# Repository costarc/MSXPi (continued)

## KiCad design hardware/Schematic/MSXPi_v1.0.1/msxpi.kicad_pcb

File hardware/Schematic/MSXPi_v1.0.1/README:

1.0.3 - Shifted PCB holes to better fit in Patola (Brazilian) case & added 3rd mounting hole
1.0.2 - Changed footprint to smaller size to help reducing manufacturing costs
1.0.1 - Changed ROM from 27C256 to AT28C256 with hability to be programmed from MSX-DOs
1.0 - PCB Changes from Rev.7

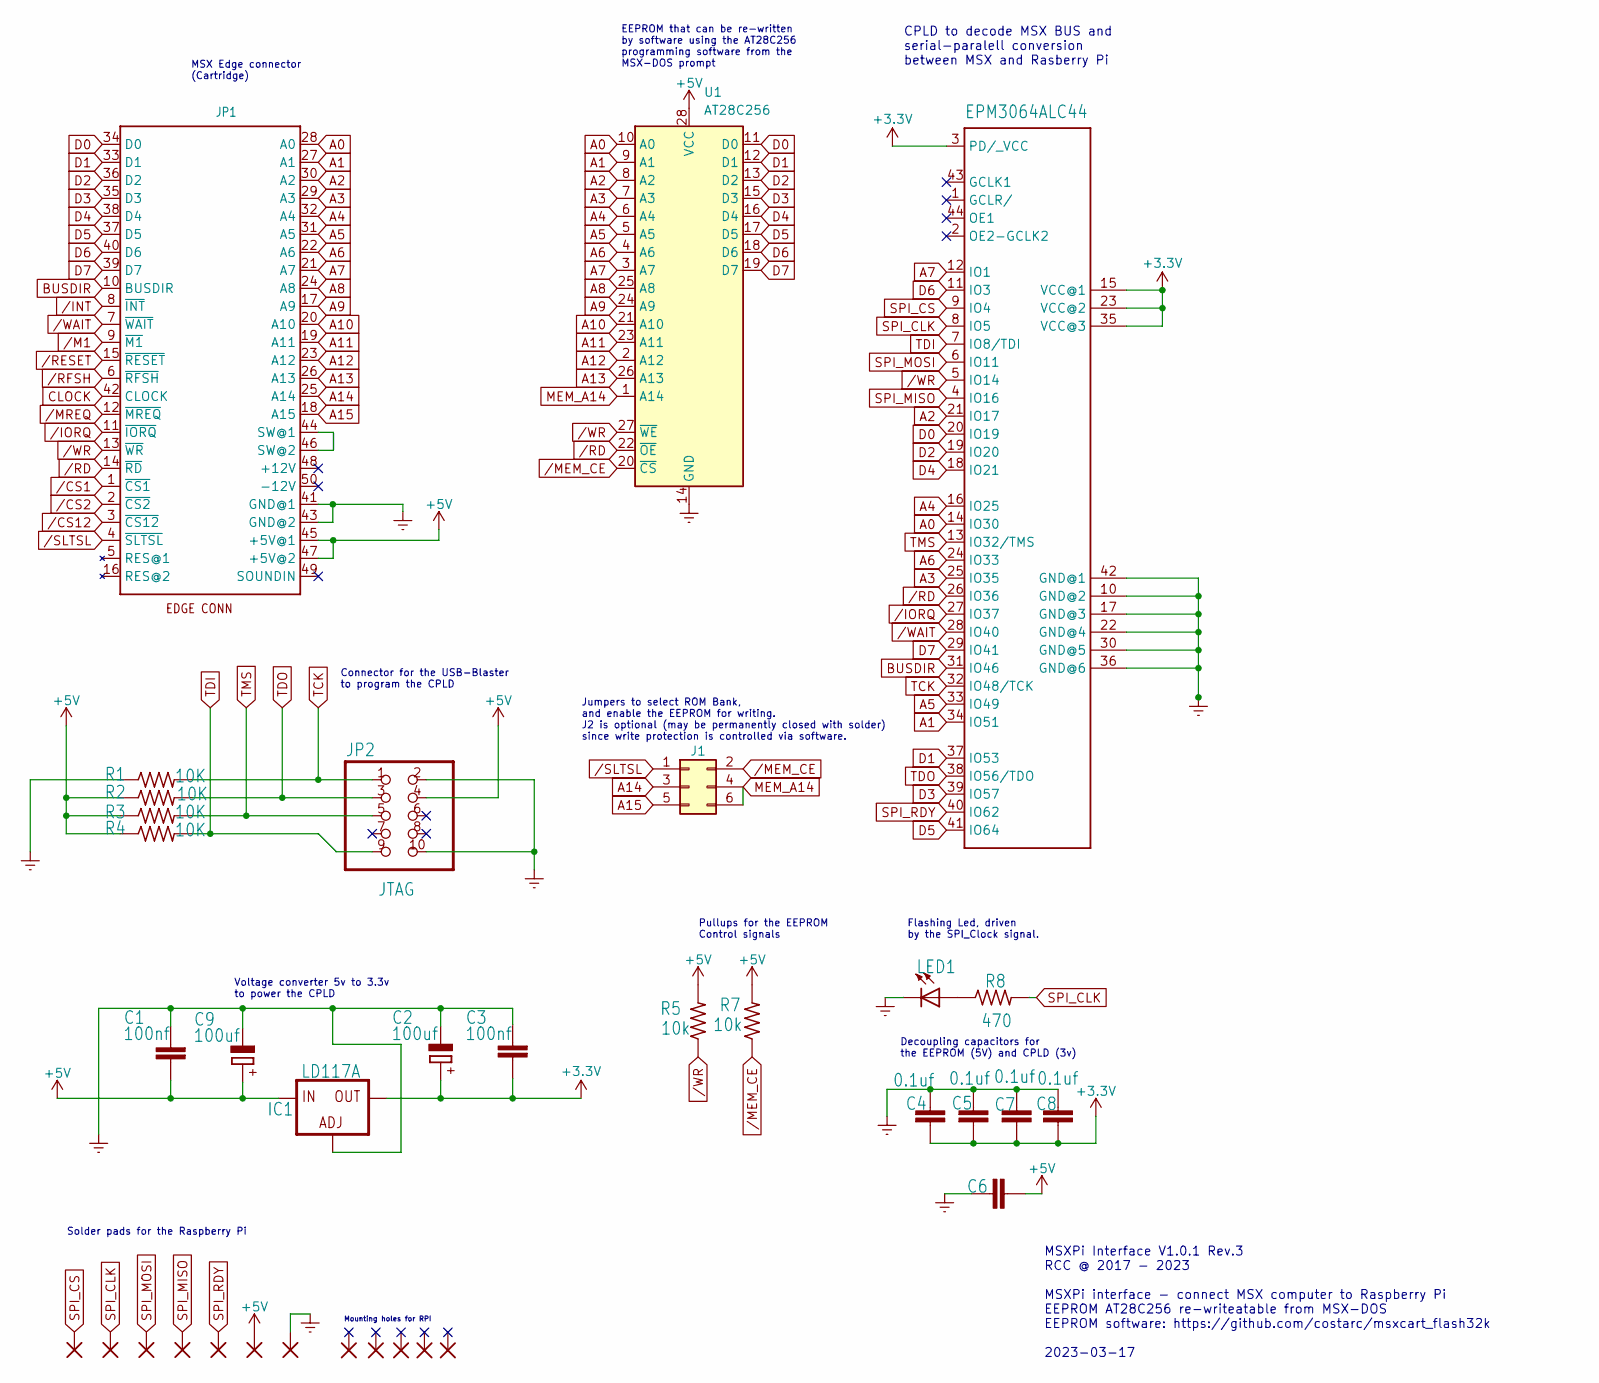
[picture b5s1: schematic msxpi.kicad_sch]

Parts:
+5V1: 2,15/1,0; 2,15_1,0
C1, C3: 100nf; C2.5-3
C2, C9: 100uf; E2,5-5
C4, C5, C6, C7, C8: 0.1uf; C2.5-3
EPM3064ALC44: EPM3064ALC44; PLCC-S44
GND5: 2,15/1,0; 2,15_1,0
IC1: LD117A; SOT-223-3_TabPin2
J1: ROM_SWITCH; PinHeader_2x03_P2.54mm_Vertical
JP1: MSXCART1; MSX_CART_SW_Official_3Holes
JP2: JTAG; IDC-Header_2x05_P2.54mm_Horizontal
LED1: LED3MM
MOUNTHOLE1, MOUNTHOLE2, MOUNTHOLE3, MOUNTHOLE4, MOUNTHOLE5: 2,15/1,0; 2,15_1,0
R1, R2, R3, R4: 10K; 0207_7
R5, R7: 10k; 0207_7
R8: 470; 0207_7
SPI_CLK_PI_GPIO1: SPI_CLK; 2,15_1,0
SPI_CS_PI_GPIO1: SPI_CS; 2,15_1,0
SPI_MISO_PI_GPIO1: SPI_MISO; 2,15_1,0
SPI_MOSI_PI_GPIO1: SPI_MOSI; 2,15_1,0
SPI_RDY_PI_GPIO1: SPI_RDY; 2,15_1,0
U1: AT28C256; DIP-28_W15.24mm

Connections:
+3.3V: C2.+, C3.1, C4.2, C5.2, C7.2, C8.2, EPM3064ALC44.3 (PD/_VCC), EPM3064ALC44.15 (VCC@1), EPM3064ALC44.23 (VCC@2), EPM3064ALC44.35 (VCC@3), IC1.2 (OUT)
+5V: +5V1.1, C1.1, C6.1, C9.+, IC1.3 (IN), JP1.45 (+5V@1), JP1.47 (+5V@2), JP2.4, R2.1, R3.1, R4.1, R5.2, R7.2, U1.28 (VCC)
A0: EPM3064ALC44.14 (IO30), JP1.28 (A0), U1.10 (A0)
A1: EPM3064ALC44.34 (IO51), JP1.27 (A1), U1.9 (A1)
A2: EPM3064ALC44.21 (IO17), JP1.30 (A2), U1.8 (A2)
A3: EPM3064ALC44.25 (IO35), JP1.29 (A3), U1.7 (A3)
A4: EPM3064ALC44.16 (IO25), JP1.32 (A4), U1.6 (A4)
A5: EPM3064ALC44.33 (IO49), JP1.31 (A5), U1.5 (A5)
A6: EPM3064ALC44.24 (IO33), JP1.22 (A6), U1.4 (A6)
A7: EPM3064ALC44.12 (IO1), JP1.21 (A7), U1.3 (A7)
A8: JP1.24 (A8), U1.25 (A8)
A9: JP1.17 (A9), U1.24 (A9)
A10: JP1.20 (A10), U1.21 (A10)
A11: JP1.19 (A11), U1.23 (A11)
A12: JP1.23 (A12), U1.2 (A12)
A13: JP1.26 (A13), U1.26 (A13)
A14: J1.3, JP1.25 (A14)
A15: J1.5, JP1.18 (A15)
BUSDIR: EPM3064ALC44.31 (IO46), JP1.10 (BUSDIR)
CLOCK: JP1.42 (CLOCK)
D0: EPM3064ALC44.20 (IO19), JP1.34 (D0), U1.11 (D0)
D1: EPM3064ALC44.37 (IO53), JP1.33 (D1), U1.12 (D1)
D2: EPM3064ALC44.19 (IO20), JP1.36 (D2), U1.13 (D2)
D3: EPM3064ALC44.39 (IO57), JP1.35 (D3), U1.15 (D3)
D4: EPM3064ALC44.18 (IO21), JP1.38 (D4), U1.16 (D4)
D5: EPM3064ALC44.41 (IO64), JP1.37 (D5), U1.17 (D5)
D6: EPM3064ALC44.11 (IO3), JP1.40 (D6), U1.18 (D6)
D7: EPM3064ALC44.29 (IO41), JP1.39 (D7), U1.19 (D7)
GNDREF: C1.2, C2.-, C3.2, C4.1, C5.1, C6.2, C7.1, C8.1, C9.-, EPM3064ALC44.10 (GND@2), EPM3064ALC44.17 (GND@3), EPM3064ALC44.22 (GND@4), EPM3064ALC44.30 (GND@5), EPM3064ALC44.36 (GND@6), EPM3064ALC44.42 (GND@1), GND5.1, IC1.1 (ADJ), JP1.41 (GND@1), JP1.43 (GND@2), JP2.2, JP2.10, LED1.K (C), R1.1, U1.14 (GND)
MEM_A14: J1.4, J1.6, U1.1 (A14)
unnamed: JP1.44 (SW@1), JP1.46 (SW@2)
unnamed: LED1.A, R8.1
SPI_CLK: EPM3064ALC44.8 (IO5), R8.2, SPI_CLK_PI_GPIO1.1
SPI_CS: EPM3064ALC44.9 (IO4), SPI_CS_PI_GPIO1.1
SPI_MISO: EPM3064ALC44.4 (IO16), SPI_MISO_PI_GPIO1.1
SPI_MOSI: EPM3064ALC44.6 (IO11), SPI_MOSI_PI_GPIO1.1
SPI_RDY: EPM3064ALC44.40 (IO62), SPI_RDY_PI_GPIO1.1
TCK: EPM3064ALC44.32 (IO48/TCK), JP2.1, R1.2
TDI: EPM3064ALC44.7 (IO8/TDI), JP2.9, R4.2
TDO: EPM3064ALC44.38 (IO56/TDO), JP2.3, R2.2
TMS: EPM3064ALC44.13 (IO32/TMS), JP2.5, R3.2
/CS1: JP1.1 (~CS1)
/CS2: JP1.2 (~CS2)
/CS12: JP1.3 (~CS12)
/INT: JP1.8 (~INT)
/IORQ: EPM3064ALC44.27 (IO37), JP1.11 (~IORQ)
/M1: JP1.9 (~M1)
/MEM_CE: J1.2, R7.1, U1.20 (~CS)
/MREQ: JP1.12 (~MREQ)
/RD: EPM3064ALC44.26 (IO36), JP1.14 (~RD), U1.22 (~OE)
/RESET: JP1.15 (~RESET)
/RFSH: JP1.6 (~RFSH)
/SLTSL: J1.1, JP1.4 (~SLTSL)
/WAIT: EPM3064ALC44.28 (IO40), JP1.7 (~WAIT)
/WR: EPM3064ALC44.5 (IO14), JP1.13 (~WR), R5.1, U1.27 (~WE)

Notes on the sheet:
Decoupling capacitors for the EEPROM (5V) and CPLD (3v)
Flashing Led, driven by the SPI_Clock signal.
Jumpers to select ROM Bank, and enable the EEPROM for writing. J2 is optional (may be permanently closed with solder) since write protection is controlled via software.
EEPROM that can be re-written by software using the AT28C256 programming software from the MSX-DOS prompt
Pullups for the EEPROM Control signals
Solder pads for the Raspberry Pi
MSXPi Interface V1.0.1 Rev.3 RCC @ 2017 - 2023 MSXPi interface - connect MSX computer to Raspberry Pi EEPROM AT28C256 re-writeatable from MSX-DOS EEPROM software: https://github.com/costarc/msxcart_flash32k 2023-03-17
MSX Edge connector (Cartridge)
Connector for the USB-Blaster to program the CPLD
Voltage converter 5v to 3.3v to power the CPLD
Mounting holes for RPI
CPLD to decode MSX BUS and serial-paralell conversion between MSX and Rasberry Pi

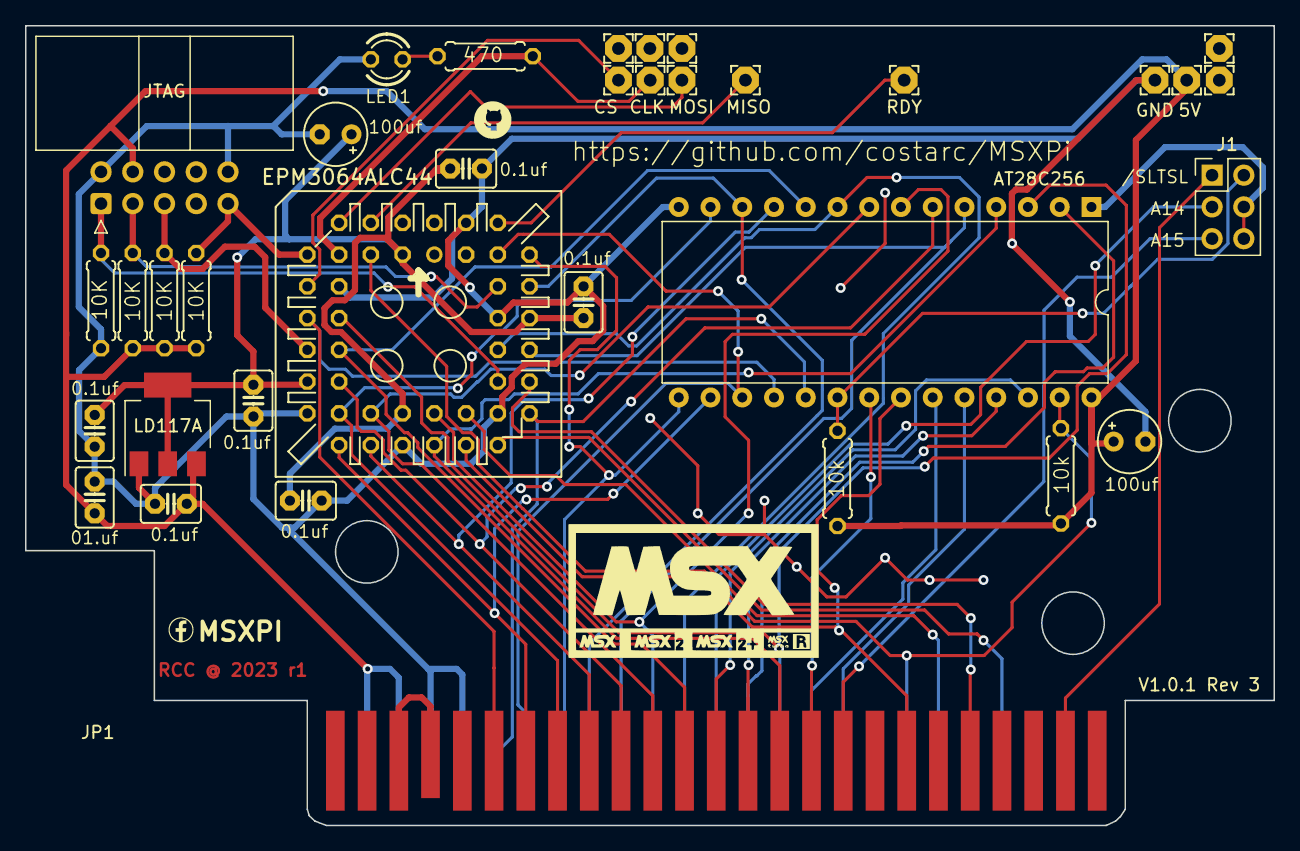
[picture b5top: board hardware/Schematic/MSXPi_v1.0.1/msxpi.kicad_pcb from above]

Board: 2 copper layers, 99.9 x 64.0 mm, 35 parts (0 on the bottom side), 46 nets.

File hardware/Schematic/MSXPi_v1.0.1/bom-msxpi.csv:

"Source:","C:\Users\alpha\Documents\Dev\MSXPi\hardware\Schematic\MSXPi_v0.7.0_Rev_7b\msxpi.kicad_sch"
"Date:","17/11/2022 13:43:14"
"Tool:","Eeschema (6.0.7)"
"Generator:","C:\KiCad\6.0\bin\scripting\plugins/bom_csv_grouped_by_value_with_fp.py"
"Component Count:","36"
"Ref","Qnty","Value","Cmp name","Footprint","Description","Vendor"
"+5V1, ","1","2,15/1,0","2,15{slash}1,0","msxpi:2,15_1,0","",""
"C1, C3, ","2","100nf","C2,5-3","msxpi:C2.5-3","",""
"C2, C9, ","2","100uf","CPOL-EUE2.5-5","msxpi:E2,5-5","",""
"C4, C5, C6, C7, C8, ","5","0.1uf","C2,5-3","msxpi:C2.5-3","",""
"EPM3064ALC44, ","1","EPM3064ALC44","EPM3064S44","msxpi:PLCC-S44","",""
"GND5, ","1","2,15/1,0","2,15{slash}1,0","msxpi:2,15_1,0","",""
"IC1, ","1","LD117A","LD117A?V","Package_TO_SOT_SMD:SOT-223-3_TabPin2","",""
"J1, ","1","ROM_SWITCH","Conn_02x07_Odd_Even","Connector_PinHeader_2.54mm:PinHeader_2x07_P2.54mm_Vertical","Generic connector, double row, 02x07, odd/even pin numbering scheme (row 1 odd numbers, row 2 even numbers), script generated (kicad-library-utils/schlib/autogen/connector/)",""
"JP1, ","1","MSXCART1","MSXCART1","Roni Footprints:MSX_CART","",""
"JP2, ","1","JTAG","PINHD-2X5{slash}90","Connector_IDC:IDC-Header_2x05_P2.54mm_Horizontal","",""
"LED1, ","1","LED3MM","LED3MM","msxpi:LED3MM","",""
"MOUNTHOLE1, MOUNTHOLE2, MOUNTHOLE3, MOUNTHOLE4, MOUNTHOLE5, ","5","2,15/1,0","2,15{slash}1,0","msxpi:2,15_1,0","",""
"R1, R2, R3, R4, ","4","10K","R-US_0207{slash}7","msxpi:0207_7","",""
"R5, R6, R7, ","3","10k","R-US_0207{slash}7","msxpi:0207_7","",""
"R8, ","1","470","R-US_0207{slash}7","msxpi:0207_7","",""
"SPI_CLK_PI_GPIO1, ","1","SPI_CLK","2,15{slash}1,0","msxpi:2,15_1,0","",""
"SPI_CS_PI_GPIO1, ","1","SPI_CS","2,15{slash}1,0","msxpi:2,15_1,0","",""
"SPI_MISO_PI_GPIO1, ","1","SPI_MISO","2,15{slash}1,0","msxpi:2,15_1,0","",""
"SPI_MOSI_PI_GPIO1, ","1","SPI_MOSI","2,15{slash}1,0","msxpi:2,15_1,0","",""
"SPI_RDY_PI_GPIO1, ","1","SPI_RDY","2,15{slash}1,0","msxpi:2,15_1,0","",""
"U1, ","1","AT28C256","28C256","Package_DIP:DIP-28_W15.24mm","Paged Parallel EEPROM 256Kb (32K x 8), DIP-28/SOIC-28",""

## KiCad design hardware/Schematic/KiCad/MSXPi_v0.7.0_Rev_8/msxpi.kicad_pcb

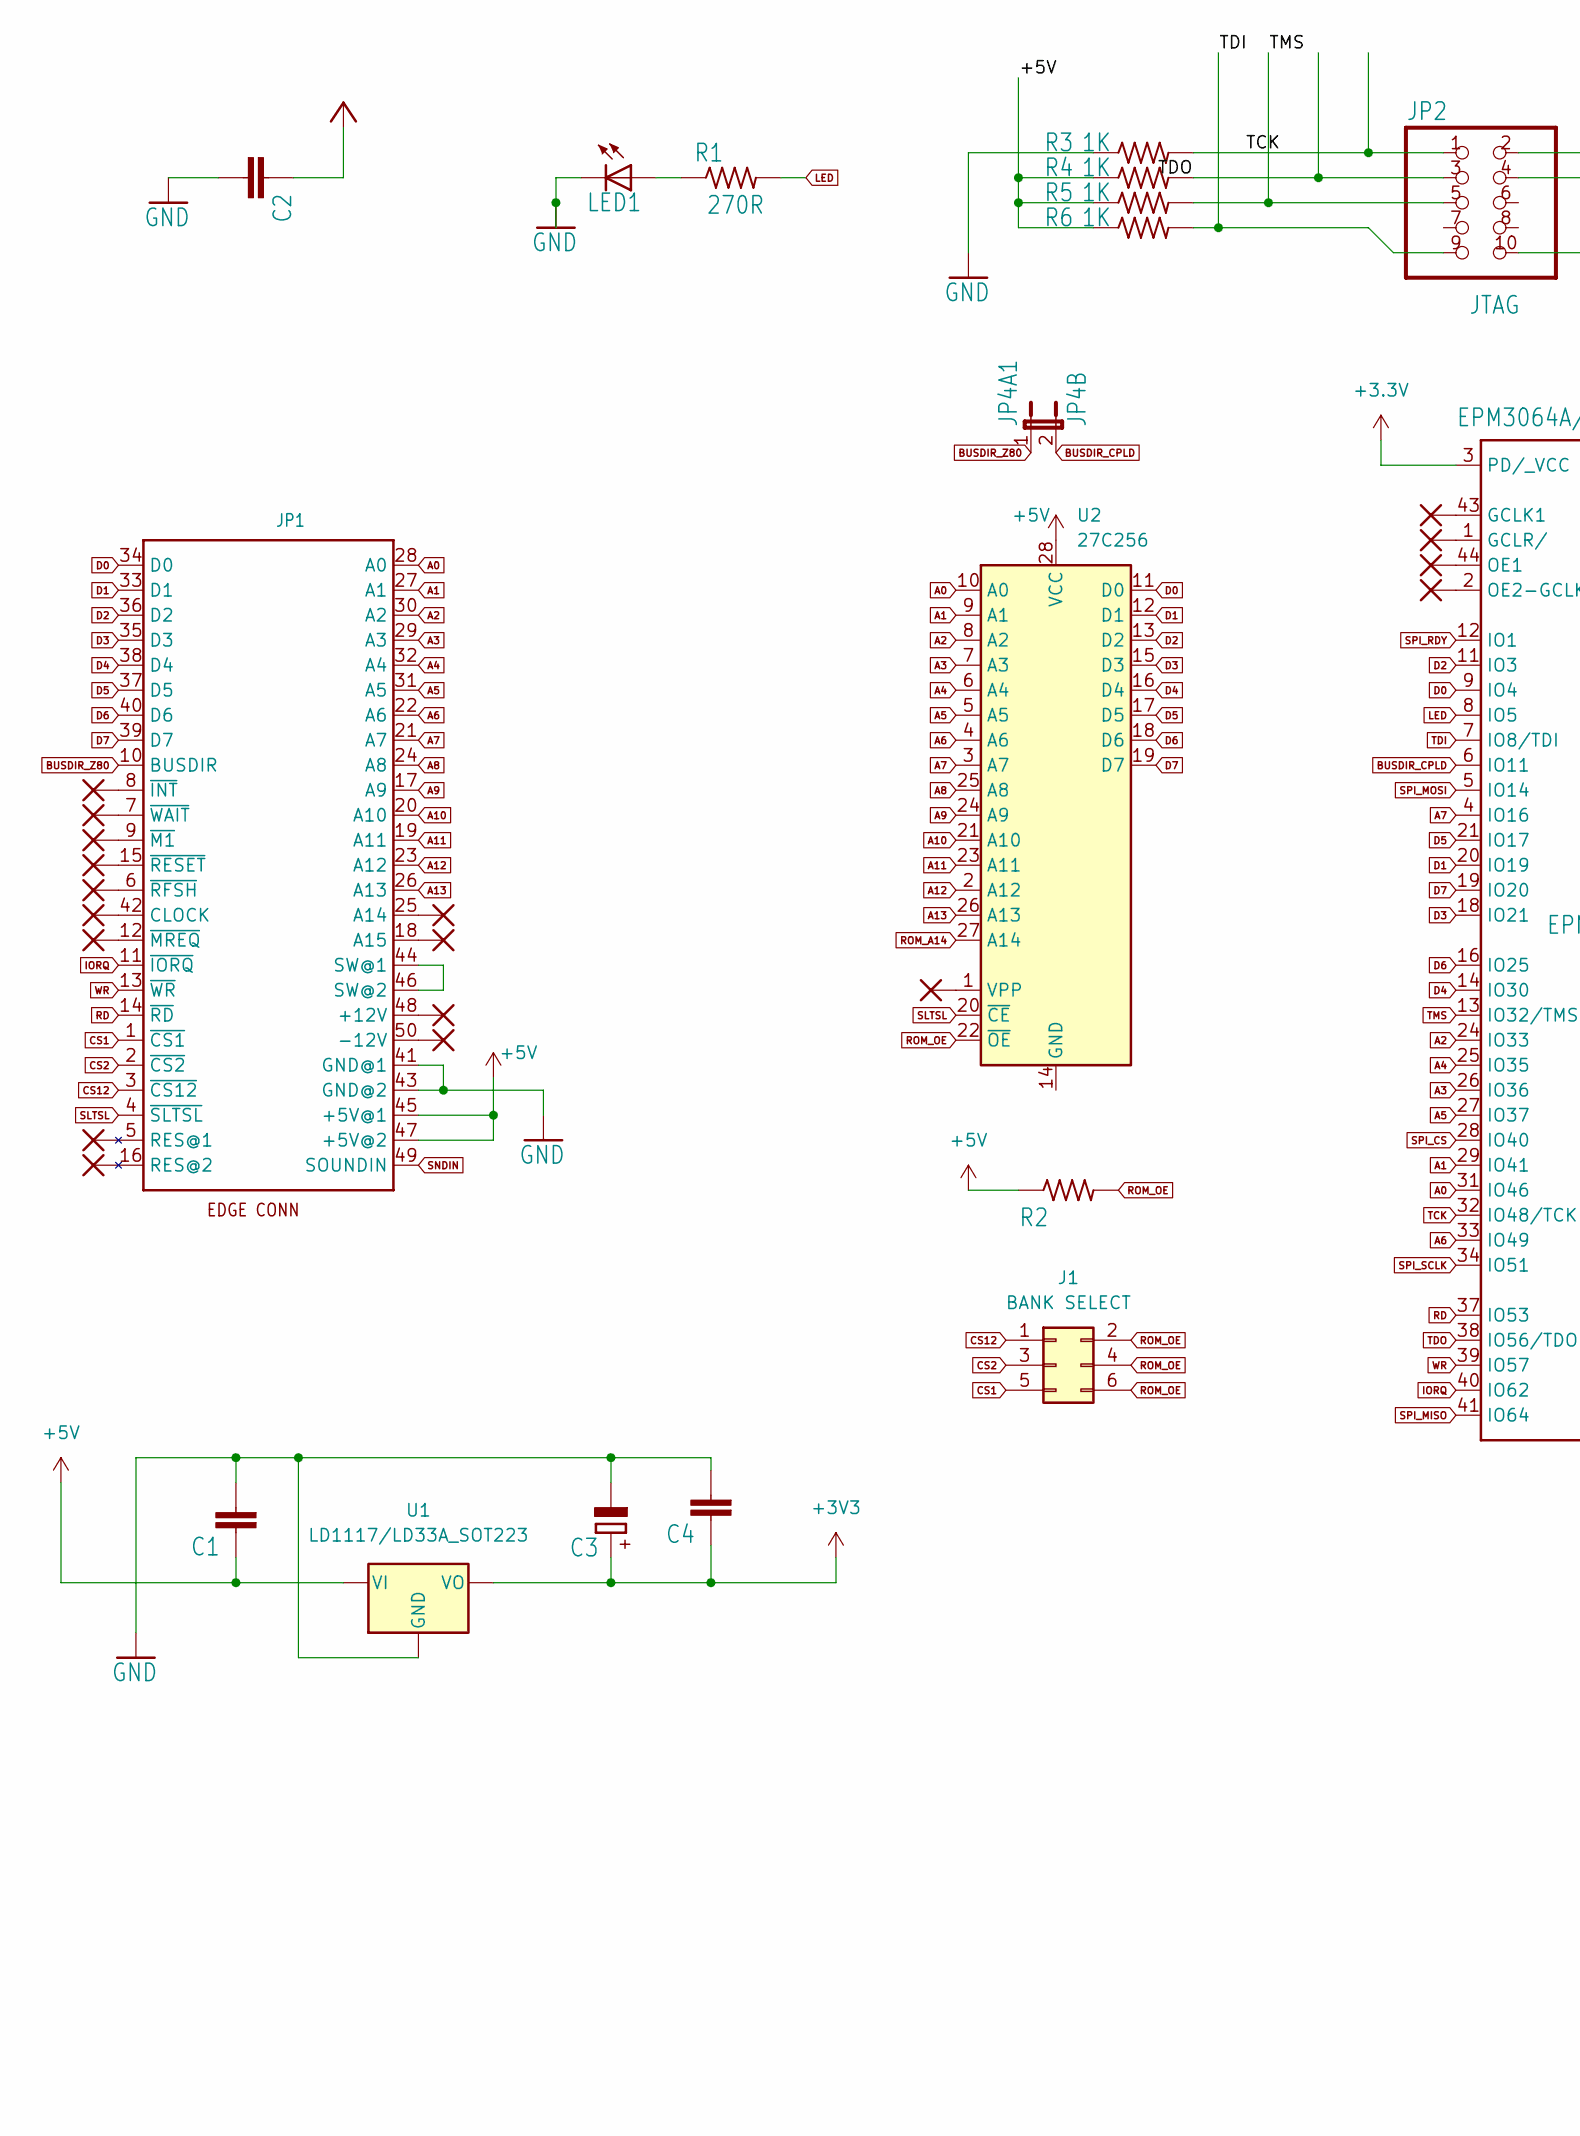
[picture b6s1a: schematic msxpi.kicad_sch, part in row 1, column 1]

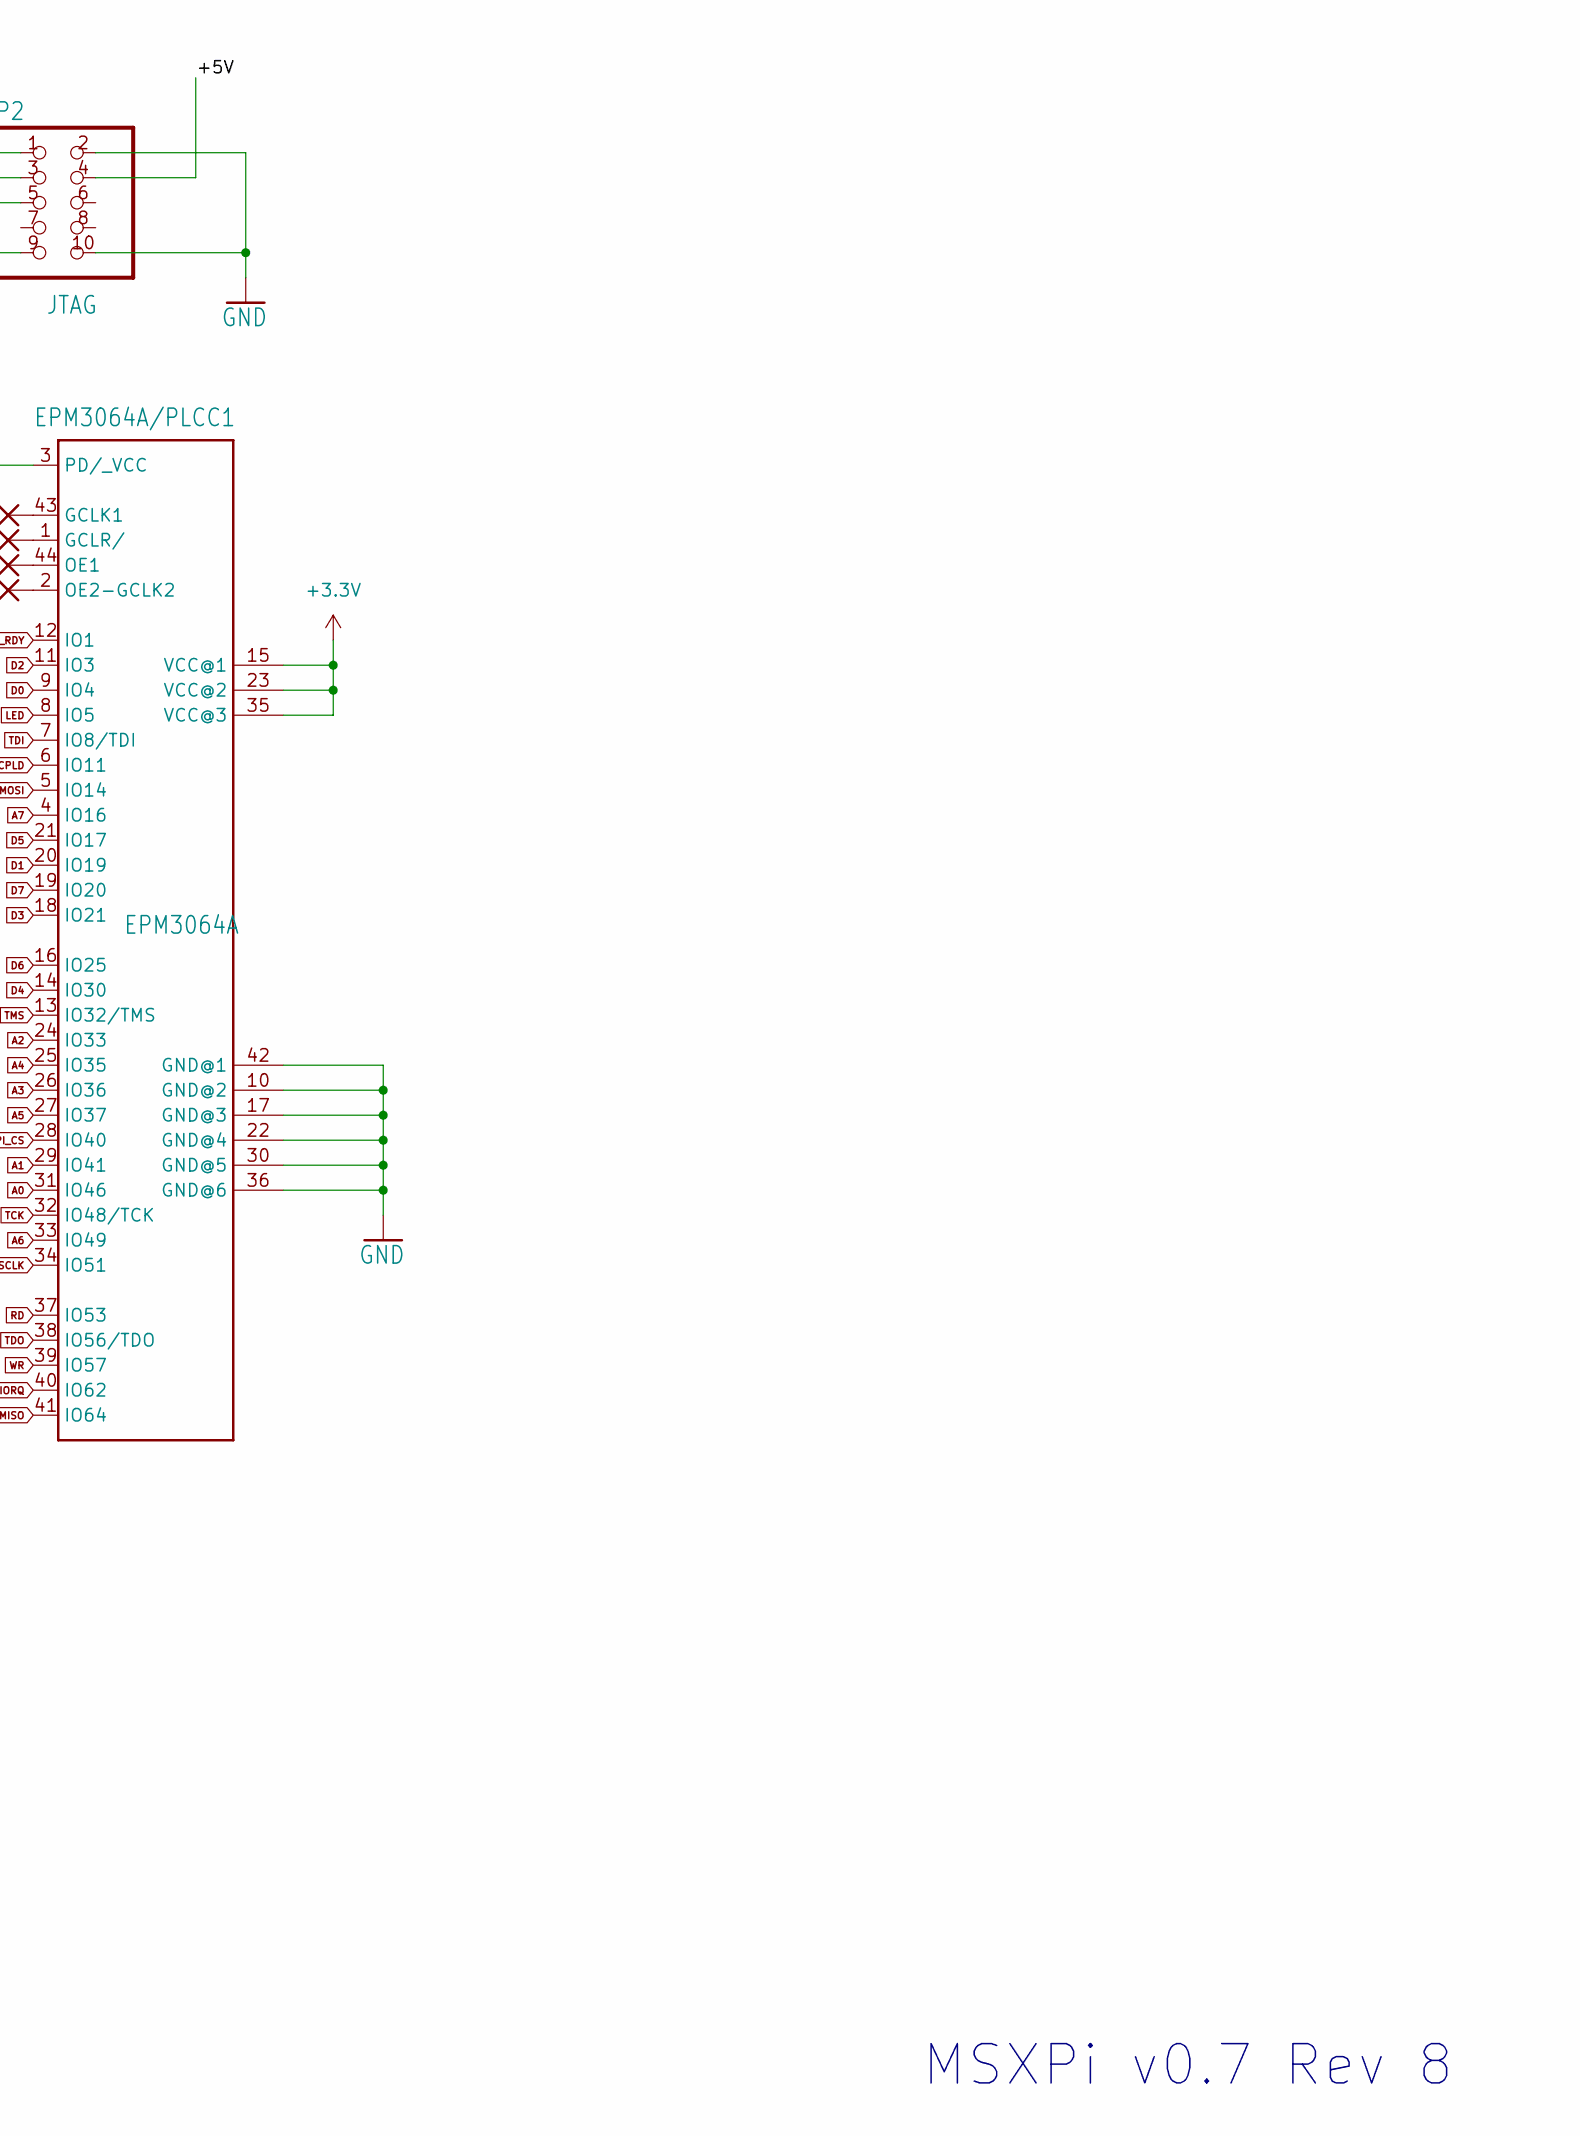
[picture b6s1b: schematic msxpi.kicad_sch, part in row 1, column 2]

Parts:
C1, C2, C4: C2,5-3; C2.5-3
C3: CPOL-EUE2.5-5; E2,5-5
CS1, CS2, CS3, CS4, CS5, CS6, CS7, CS8, CS9, CS10, CS11, CS12, CS13, CS14, CS15, CS16, CS17: 2,15/1,0; 2,15_1,0
EPM3064A/PLCC1: EPM3064A; PLCC-S44
J1: BANK SELECT; PinHeader_2x03_P2.54mm_Vertical
JP1: MSXCART1; MSXCART
JP2: JTAG; 2X05_90
JP4A1: JP4B; JP1
LED1: LED3MM
PAD1: 2,15/1,0; 2,15_1,0
R1: 270R; 0207_7
R2: R-US_0207/7; 0207_7
R3, R4, R5, R6: 1K; 0207_7
U1: LD1117/LD33A_SOT223; SOT-223-3_TabPin2
U2: 27C256; DIP-28_W15.24mm

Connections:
+3.3V: EPM3064A/PLCC1.3 (PD/_VCC), EPM3064A/PLCC1.15 (VCC@1), EPM3064A/PLCC1.23 (VCC@2), EPM3064A/PLCC1.35 (VCC@3)
+3V3: C3.+, C4.1, U1.2 (VO)
+5V: C1.1, JP1.45 (+5V@1), JP1.47 (+5V@2), JP2.4, R2.1, R4.1, R5.1, R6.1, U1.3 (VI), U2.28 (VCC)
A0: EPM3064A/PLCC1.31 (IO46), JP1.28 (A0), U2.10 (A0)
A1: EPM3064A/PLCC1.29 (IO41), JP1.27 (A1), U2.9 (A1)
A2: EPM3064A/PLCC1.24 (IO33), JP1.30 (A2), U2.8 (A2)
A3: EPM3064A/PLCC1.26 (IO36), JP1.29 (A3), U2.7 (A3)
A4: EPM3064A/PLCC1.25 (IO35), JP1.32 (A4), U2.6 (A4)
A5: EPM3064A/PLCC1.27 (IO37), JP1.31 (A5), U2.5 (A5)
A6: EPM3064A/PLCC1.33 (IO49), JP1.22 (A6), U2.4 (A6)
A7: EPM3064A/PLCC1.4 (IO16), JP1.21 (A7), U2.3 (A7)
A8: JP1.24 (A8), U2.25 (A8)
A9: JP1.17 (A9), U2.24 (A9)
A10: JP1.20 (A10), U2.21 (A10)
A11: JP1.19 (A11), U2.23 (A11)
A12: JP1.23 (A12), U2.2 (A12)
A13: JP1.26 (A13), U2.26 (A13)
BUSDIR_CPLD: EPM3064A/PLCC1.6 (IO11), JP4A1.2
BUSDIR_Z80: JP1.10 (BUSDIR), JP4A1.1
CS1: J1.5, JP1.1 (~CS1)
CS2: J1.3, JP1.2 (~CS2)
CS12: J1.1, JP1.3 (~CS12)
D0: EPM3064A/PLCC1.9 (IO4), JP1.34 (D0), U2.11 (D0)
D1: EPM3064A/PLCC1.20 (IO19), JP1.33 (D1), U2.12 (D1)
D2: EPM3064A/PLCC1.11 (IO3), JP1.36 (D2), U2.13 (D2)
D3: EPM3064A/PLCC1.18 (IO21), JP1.35 (D3), U2.15 (D3)
D4: EPM3064A/PLCC1.14 (IO30), JP1.38 (D4), U2.16 (D4)
D5: EPM3064A/PLCC1.21 (IO17), JP1.37 (D5), U2.17 (D5)
D6: EPM3064A/PLCC1.16 (IO25), JP1.40 (D6), U2.18 (D6)
D7: EPM3064A/PLCC1.19 (IO20), JP1.39 (D7), U2.19 (D7)
GND: C1.2, C2.2, C3.-, C4.2, EPM3064A/PLCC1.10 (GND@2), EPM3064A/PLCC1.17 (GND@3), EPM3064A/PLCC1.22 (GND@4), EPM3064A/PLCC1.30 (GND@5), EPM3064A/PLCC1.36 (GND@6), EPM3064A/PLCC1.42 (GND@1), JP1.41 (GND@1), JP1.43 (GND@2), JP2.2, JP2.10, LED1.K (C), R3.1, U1.1 (GND)
IORQ: EPM3064A/PLCC1.40 (IO62), JP1.11 (~IORQ)
LED: EPM3064A/PLCC1.8 (IO5), R1.2
unnamed: CS1.1, JP1.8 (~INT)
unnamed: CS2.1, JP1.7 (~WAIT)
unnamed: CS3.1, JP1.9 (~M1)
unnamed: CS4.1, JP1.15 (~RESET)
unnamed: CS5.1, JP1.6 (~RFSH)
unnamed: CS6.1, JP1.42 (CLOCK)
unnamed: CS7.1, JP1.12 (~MREQ)
unnamed: CS9.1, JP1.25 (A14)
unnamed: CS10.1, JP1.18 (A15)
unnamed: CS11.1, JP1.48 (+12V)
unnamed: CS12.1, JP1.50 (-12V)
unnamed: CS13.1, U2.1 (VPP)
unnamed: CS14.1, EPM3064A/PLCC1.43 (GCLK1)
unnamed: CS15.1, EPM3064A/PLCC1.1 (GCLR/)
unnamed: CS16.1, EPM3064A/PLCC1.44 (OE1)
unnamed: CS17.1, EPM3064A/PLCC1.2 (OE2-GCLK2)
unnamed: JP1.44 (SW@1), JP1.46 (SW@2)
unnamed: LED1.A, R1.1
RD: EPM3064A/PLCC1.37 (IO53), JP1.14 (~RD)
ROM_A14: U2.27 (A14)
ROM_OE: J1.2, J1.4, J1.6, R2.2, U2.22 (~OE)
SLTSL: JP1.4 (~SLTSL), U2.20 (~CE)
SNDIN: JP1.49 (SOUNDIN)
SPI_CS: EPM3064A/PLCC1.28 (IO40)
SPI_MISO: EPM3064A/PLCC1.41 (IO64)
SPI_MOSI: EPM3064A/PLCC1.5 (IO14)
SPI_RDY: EPM3064A/PLCC1.12 (IO1)
SPI_SCLK: EPM3064A/PLCC1.34 (IO51)
TCK: EPM3064A/PLCC1.32 (IO48/TCK), JP2.1, R3.2
TDI: EPM3064A/PLCC1.7 (IO8/TDI), JP2.9, R6.2
TDO: EPM3064A/PLCC1.38 (IO56/TDO), JP2.3, R4.2
TMS: EPM3064A/PLCC1.13 (IO32/TMS), JP2.5, R5.2
VCC: C2.1
WR: EPM3064A/PLCC1.39 (IO57), JP1.13 (~WR)

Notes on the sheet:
MSXPi v0.7 Rev 8

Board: 2 copper layers, 36 parts (0 on the bottom side), 59 nets, no tracks yet.
